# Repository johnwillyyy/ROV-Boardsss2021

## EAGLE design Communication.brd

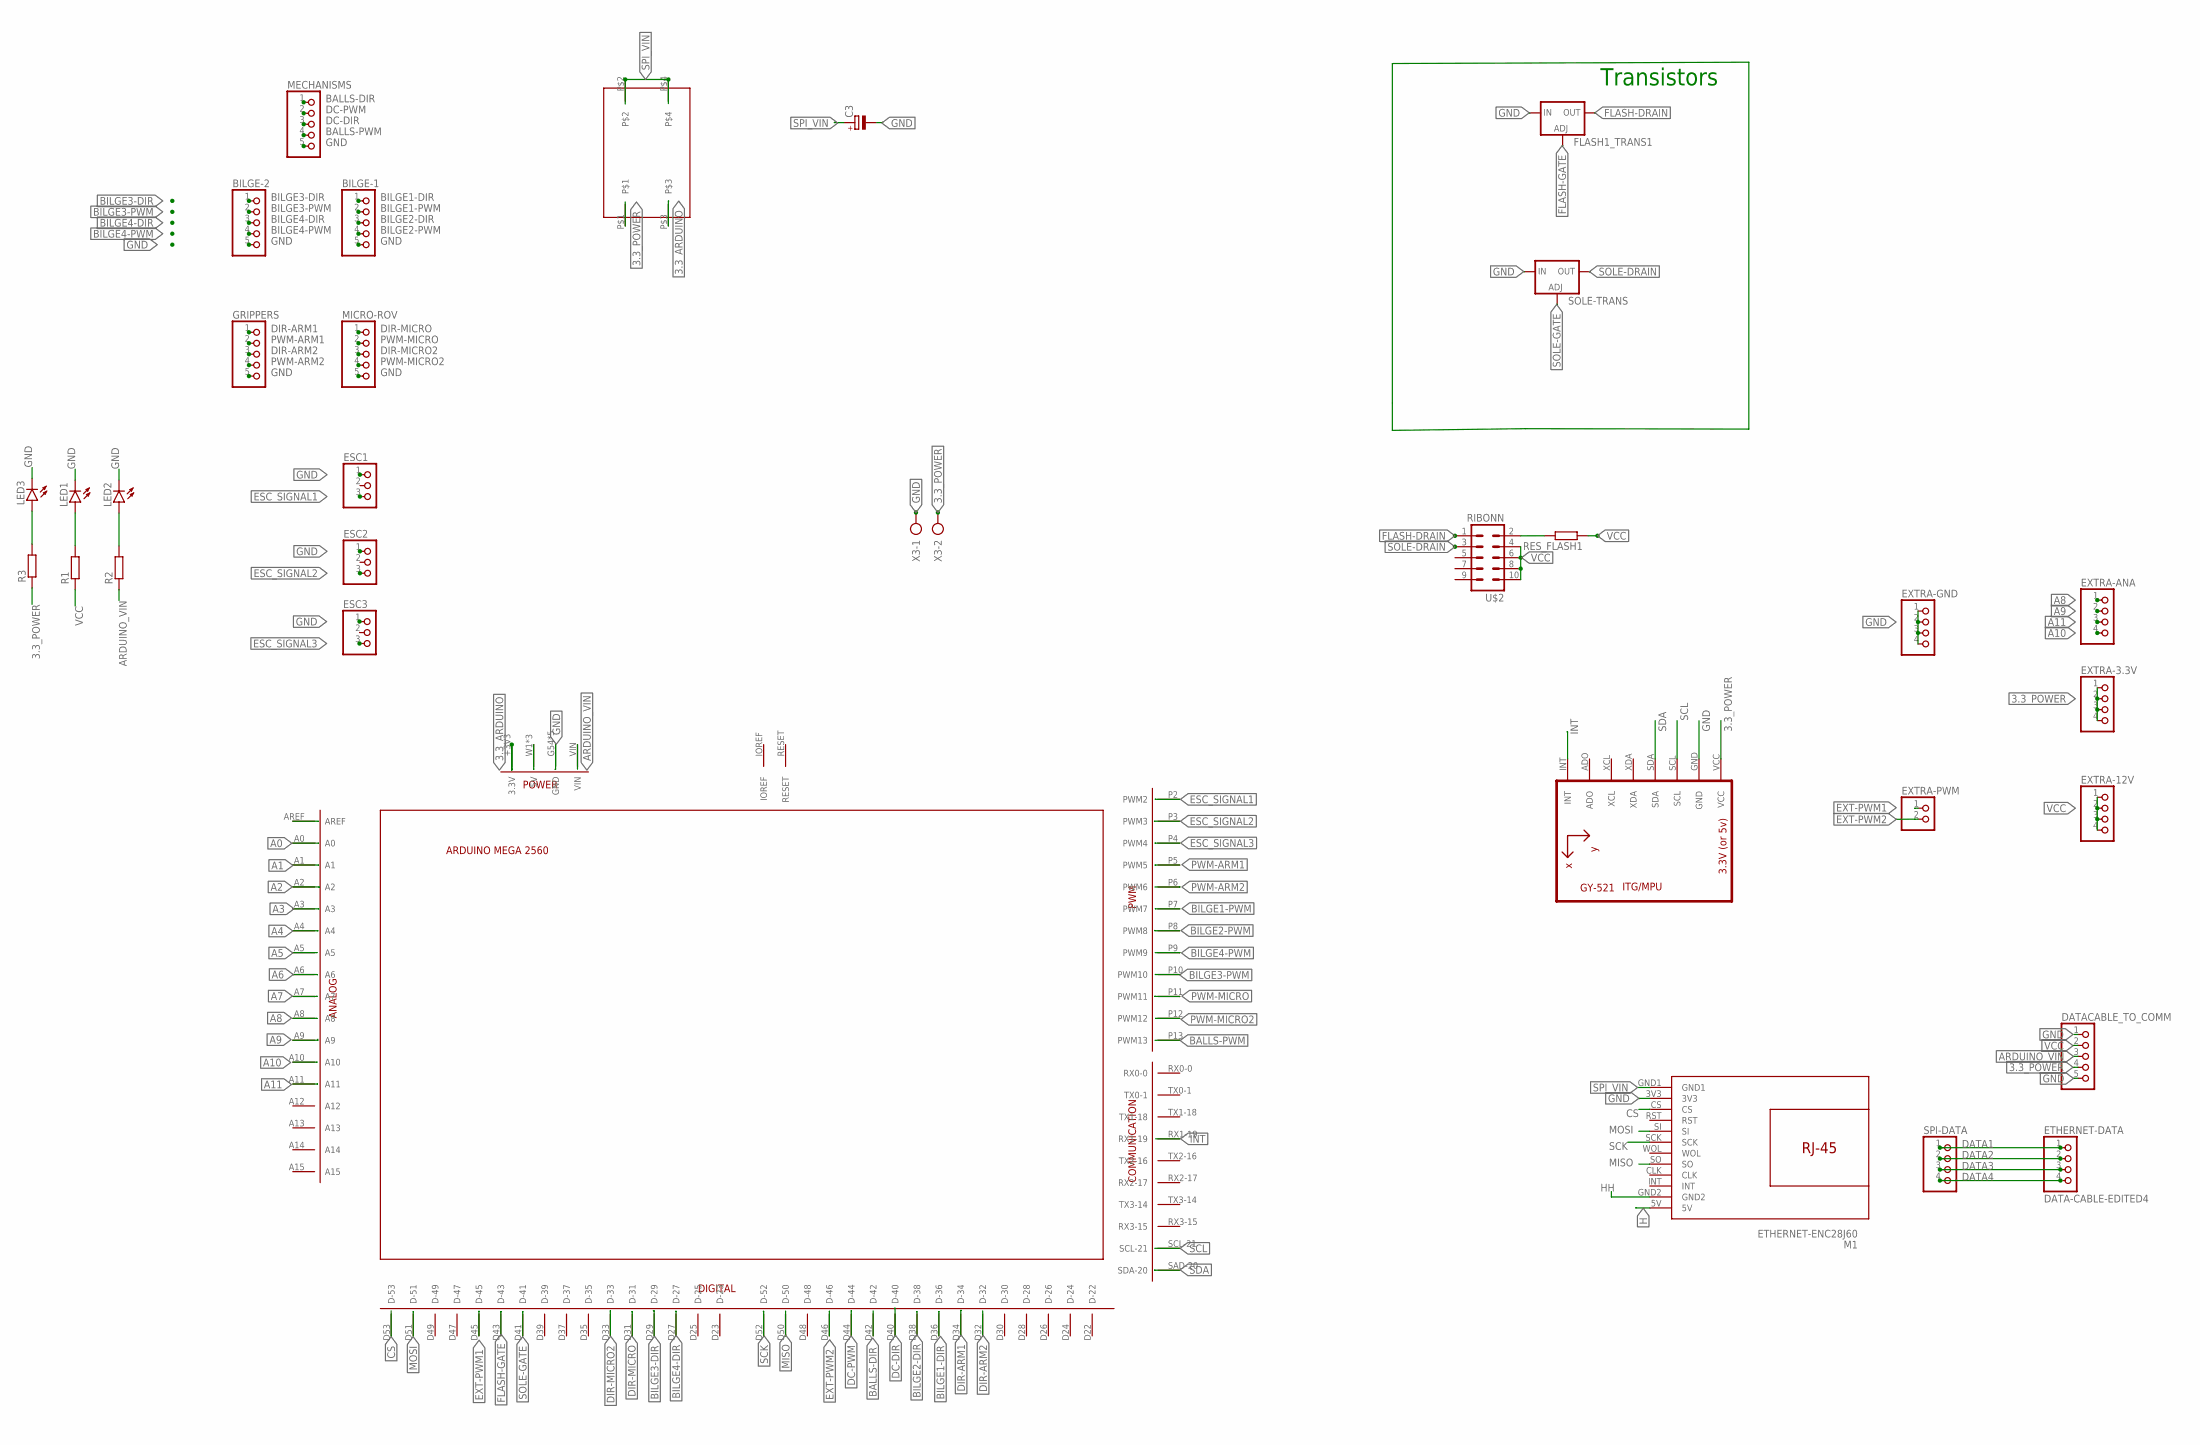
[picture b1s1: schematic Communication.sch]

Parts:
BILGE-1, BILGE-2: PINHD-1X5; 1X05
C3: CPOL-EUE3.5-8; E3,5-8
DATACABLE_TO_COMM: PINHD-1X5; 1X05
ESC1, ESC2, ESC3: PINHD-1X3; 1X03
ETHERNET-DATA: DATA-CABLE-EDITED4
EXTRA-3.3V, EXTRA-12V: PINHD-1X4; 1X04
EXTRA-ANA: PINHD-1X4; 1X04
EXTRA-GND: PINHD-1X4; 1X04
EXTRA-PWM: PINHD-1X2; 1X02
FLASH1_TRANS1: LM317TS; 317TS
GRIPPERS: PINHD-1X5; 1X05
LED1, LED2, LED3: LED3MM
M1: ETHERNET-ENC28J60
MECHANISMS: PINHD-1X5; 1X05
MICRO-ROV: PINHD-1X5; 1X05
R1, R2, R3: R-EU_0207/10; 0207/10
RES_FLASH1: R-EU_0207/10; 0207/10
SOLE-TRANS: LM317TS; 317TS
SPI-DATA: PINHD-1X4; 1X04
U2: GY-521MPU6050; GY-521
U$1: BOARD_ARDUINO-MEGA; BOARD_ARDUINO_MEGA
U$2: RIBONN
U$3: DIPSWITCH_2PINS
X3: AK300/2

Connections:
3.3_ARDUINO: U$1.+3V3 (3.3V), U$3.P$3
3.3_POWER: DATACABLE_TO_COMM.4, EXTRA-3.3V.1, EXTRA-3.3V.2, EXTRA-3.3V.3, EXTRA-3.3V.4, R3.1, U2.VCC, U$3.P$1, X3.2
A0: U$1.A0
A1: U$1.A1
A2: U$1.A2
A3: U$1.A3
A4: U$1.A4
A5: U$1.A5
A6: U$1.A6
A7: U$1.A7
A8: EXTRA-ANA.1, U$1.A8
A9: EXTRA-ANA.2, U$1.A9
A10: EXTRA-ANA.4, U$1.A10
A11: EXTRA-ANA.3, U$1.A11
ARDUINO_VIN: DATACABLE_TO_COMM.3, R2.1, U$1.VIN
BALLS-DIR: MECHANISMS.1, U$1.D42 (D-42)
BALLS-PWM: MECHANISMS.4, U$1.P13 (PWM13)
BILGE1-DIR: BILGE-1.1, U$1.D36 (D-36)
BILGE1-PWM: BILGE-1.2, U$1.P7 (PWM7)
BILGE2-DIR: BILGE-1.3, U$1.D38 (D-38)
BILGE2-PWM: BILGE-1.4, U$1.P8 (PWM8)
BILGE3-DIR: BILGE-2.1, U$1.D29 (D-29)
BILGE3-PWM: BILGE-2.2, U$1.P10 (PWM10)
BILGE4-DIR: BILGE-2.3, U$1.D27 (D-27)
BILGE4-PWM: BILGE-2.4, U$1.P9 (PWM9)
CS: M1.CS, U$1.D53 (D-53)
DATA1: ETHERNET-DATA.1, SPI-DATA.1
DATA2: ETHERNET-DATA.2, SPI-DATA.2
DATA3: ETHERNET-DATA.3, SPI-DATA.3
DATA4: ETHERNET-DATA.4, SPI-DATA.4
DC-DIR: MECHANISMS.3, U$1.D40 (D-40)
DC-PWM: MECHANISMS.2, U$1.D44 (D-44)
DIR-ARM1: GRIPPERS.1, U$1.D34 (D-34)
DIR-ARM2: GRIPPERS.3, U$1.D32 (D-32)
DIR-MICRO: MICRO-ROV.1, U$1.D31 (D-31)
DIR-MICRO2: MICRO-ROV.3, U$1.D33 (D-33)
ESC_SIGNAL1: ESC1.3, U$1.P2 (PWM2)
ESC_SIGNAL2: ESC2.3, U$1.P3 (PWM3)
ESC_SIGNAL3: ESC3.3, U$1.P4 (PWM4)
EXT-PWM1: EXTRA-PWM.1, U$1.D45 (D-45)
EXT-PWM2: EXTRA-PWM.2, U$1.D46 (D-46)
FLASH-DRAIN: FLASH1_TRANS1.2 (OUT), U$2.1
FLASH-GATE: FLASH1_TRANS1.1 (ADJ), U$1.D43 (D-43)
GND: BILGE-1.5, BILGE-2.5, C3.-, DATACABLE_TO_COMM.1, DATACABLE_TO_COMM.5, ESC1.1, ESC2.1, ESC3.1, EXTRA-GND.1, EXTRA-GND.2, EXTRA-GND.3, EXTRA-GND.4, FLASH1_TRANS1.3 (IN), GRIPPERS.5, LED1.K (C), LED2.K (C), LED3.K (C), M1.3V3, MECHANISMS.5, MICRO-ROV.5, SOLE-TRANS.3 (IN), U2.GND, U$1.G54 (GND), U$1.G55 (GND), U$1.G56 (GND), U$1.G57 (GND), U$1.G58 (GND), X3.1
H: M1.5V
HH: M1.GND2
INT: U2.INT, U$1.RX1-19
MISO: M1.SO, U$1.D50 (D-50)
MOSI: M1.SI, U$1.D51 (D-51)
unnamed: LED1.A, R1.2
unnamed: LED2.A, R2.2
unnamed: RES_FLASH1.2, U$2.2
unnamed: LED3.A, R3.2
unnamed: U$1.W1 (5V), U$1.W2 (5V), U$1.W3 (5V)
PWM-ARM1: GRIPPERS.2, U$1.P5 (PWM5)
PWM-ARM2: GRIPPERS.4, U$1.P6 (PWM6)
PWM-MICRO: MICRO-ROV.2, U$1.P11 (PWM11)
PWM-MICRO2: MICRO-ROV.4, U$1.P12 (PWM12)
SCK: M1.SCK, U$1.D52 (D-52)
SCL: U2.SCL, U$1.SCL-21
SDA: U2.SDA, U$1.SAD-20 (SDA-20)
SOLE-DRAIN: SOLE-TRANS.2 (OUT), U$2.3
SOLE-GATE: SOLE-TRANS.1 (ADJ), U$1.D41 (D-41)
SPI_VIN: C3.+, M1.GND1, U$3.P$2, U$3.P$4
VCC: DATACABLE_TO_COMM.2, EXTRA-12V.1, EXTRA-12V.2, EXTRA-12V.3, EXTRA-12V.4, R1.1, RES_FLASH1.1, U$2.4, U$2.6, U$2.8, U$2.10

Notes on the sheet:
Transistors

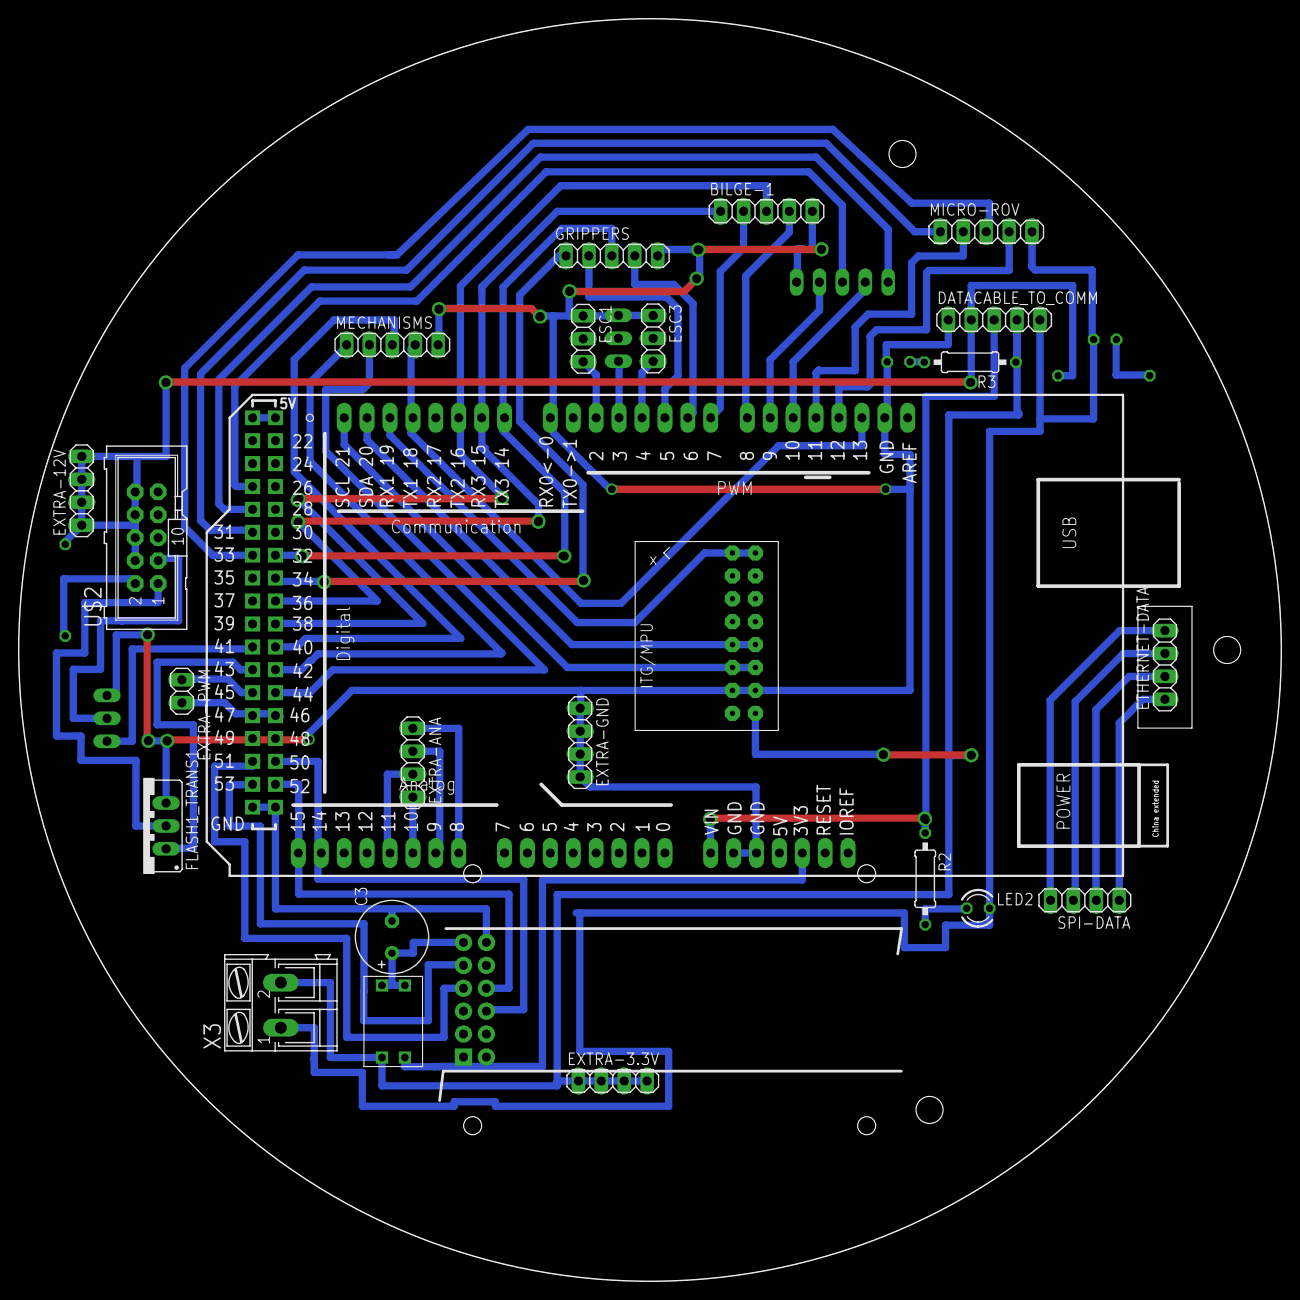
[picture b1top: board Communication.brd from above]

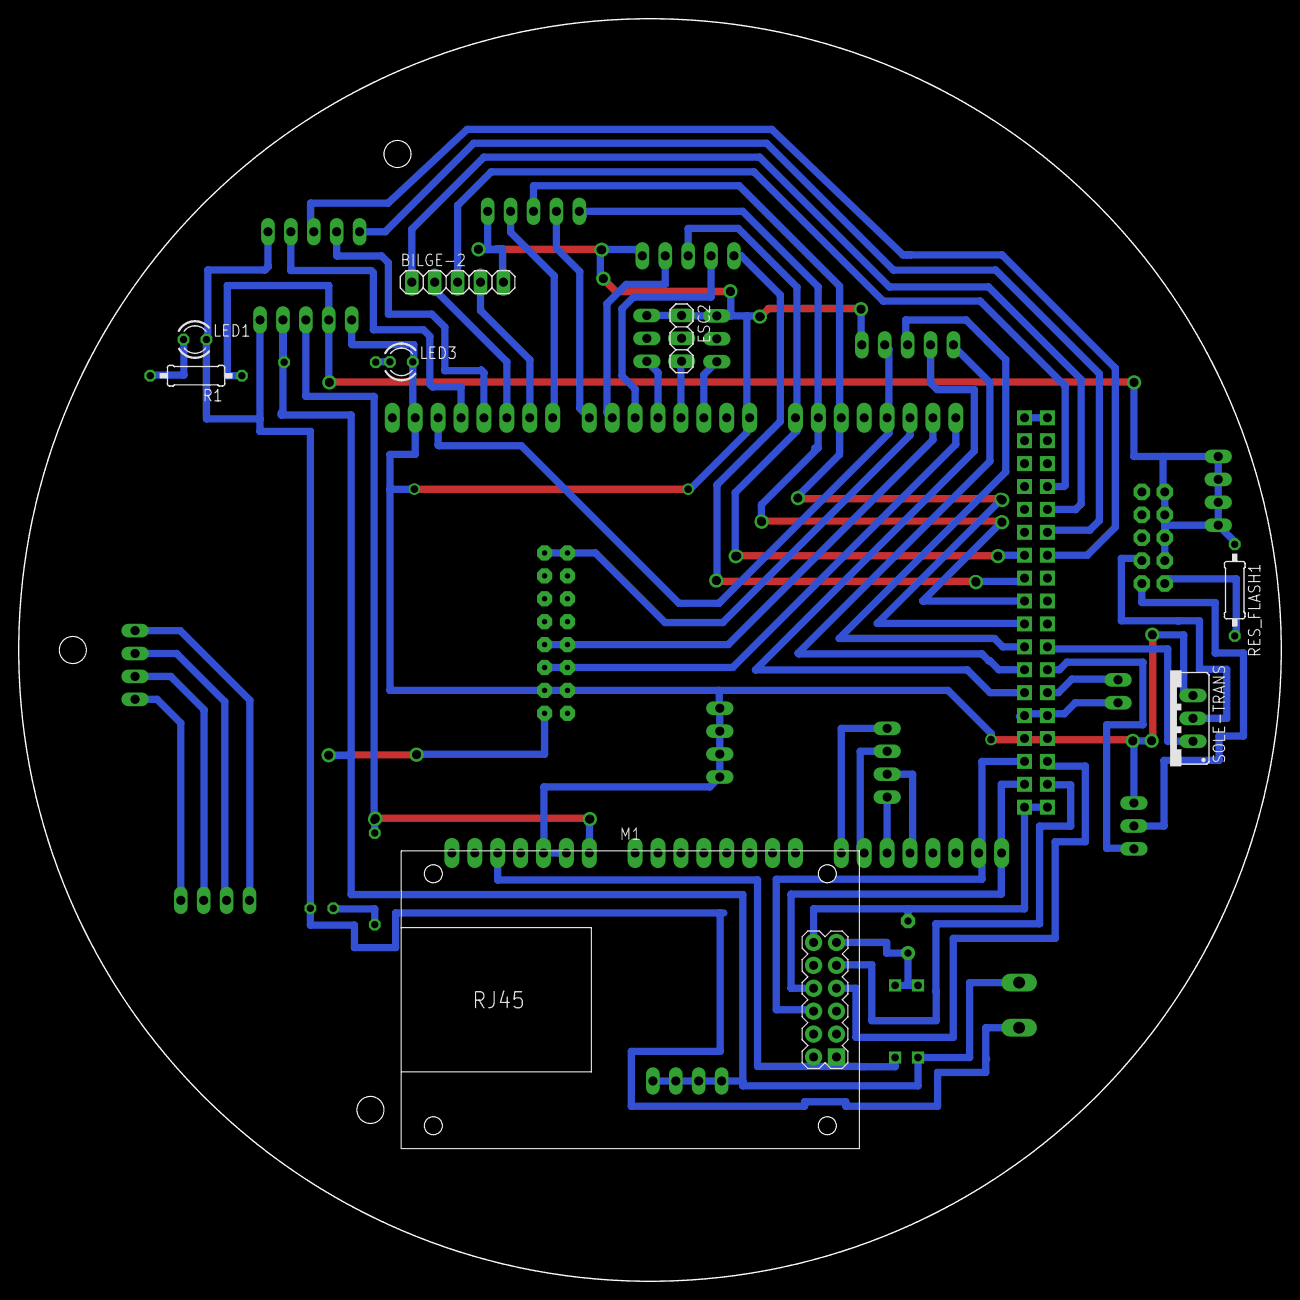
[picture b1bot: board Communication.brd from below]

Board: 2 copper layers, 140.0 x 140.0 mm, 32 parts (8 on the bottom side), 55 nets.

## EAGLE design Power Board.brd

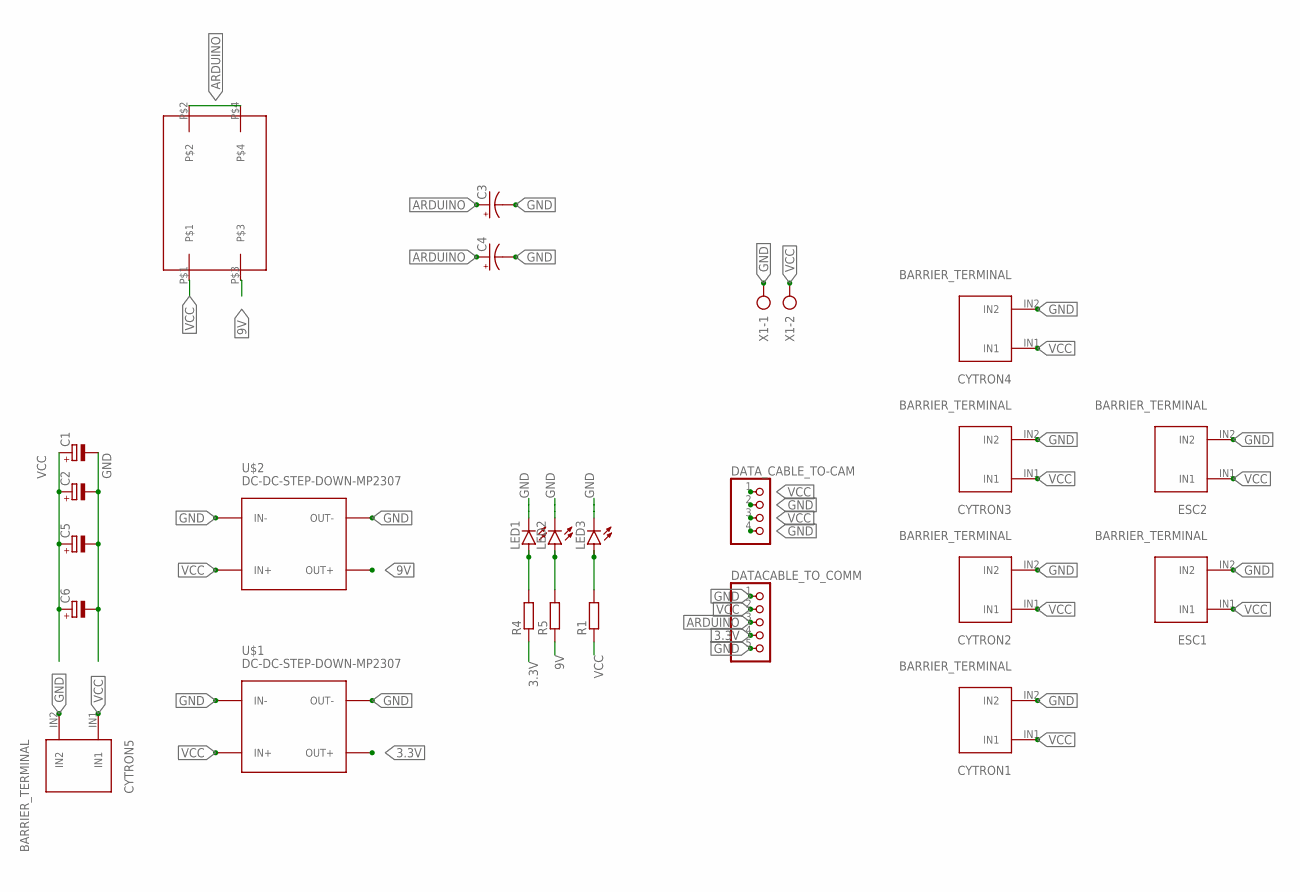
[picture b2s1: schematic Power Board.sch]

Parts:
C1, C2, C5, C6: CPOL-EUE7.5-16; E7,5-16
C3, C4: CPOL-USE5-13; E5-13
CYTRON1, CYTRON2, CYTRON3, CYTRON4, CYTRON5: BARRIER_TERMINAL
DATACABLE_TO_COMM: PINHD-1X5; 1X05
DATA_CABLE_TO-CAM: PINHD-1X4; 1X04
ESC1, ESC2: BARRIER_TERMINAL
LED1, LED2, LED3: LED3MM
R1, R4, R5: R-EU_0204/7; 0204/7
U$1, U$2: DC-DC-STEP-DOWN-MP2307
U$3: DIPSWITCH_2PINS
X1: AK300/2

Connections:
3.3V: DATACABLE_TO_COMM.4, R4.1, U$1.OUT+
9V: R5.1, U$2.OUT+, U$3.P$3
ARDUINO: C3.+, C4.+, DATACABLE_TO_COMM.3, U$3.P$2, U$3.P$4
GND: C1.-, C2.-, C3.-, C4.-, C5.-, C6.-, CYTRON1.IN2, CYTRON2.IN2, CYTRON3.IN2, CYTRON4.IN2, CYTRON5.IN2, DATACABLE_TO_COMM.1, DATACABLE_TO_COMM.5, DATA_CABLE_TO-CAM.2, DATA_CABLE_TO-CAM.4, ESC1.IN2, ESC2.IN2, LED1.K (C), LED2.K (C), LED3.K (C), U$1.IN-, U$1.OUT-, U$2.IN-, U$2.OUT-, X1.1
unnamed: LED3.A, R1.2
unnamed: LED1.A, R4.2
unnamed: LED2.A, R5.2
VCC: C1.+, C2.+, C5.+, C6.+, CYTRON1.IN1, CYTRON2.IN1, CYTRON3.IN1, CYTRON4.IN1, CYTRON5.IN1, DATACABLE_TO_COMM.2, DATA_CABLE_TO-CAM.1, DATA_CABLE_TO-CAM.3, ESC1.IN1, ESC2.IN1, R1.1, U$1.IN+, U$2.IN+, U$3.P$1, X1.2

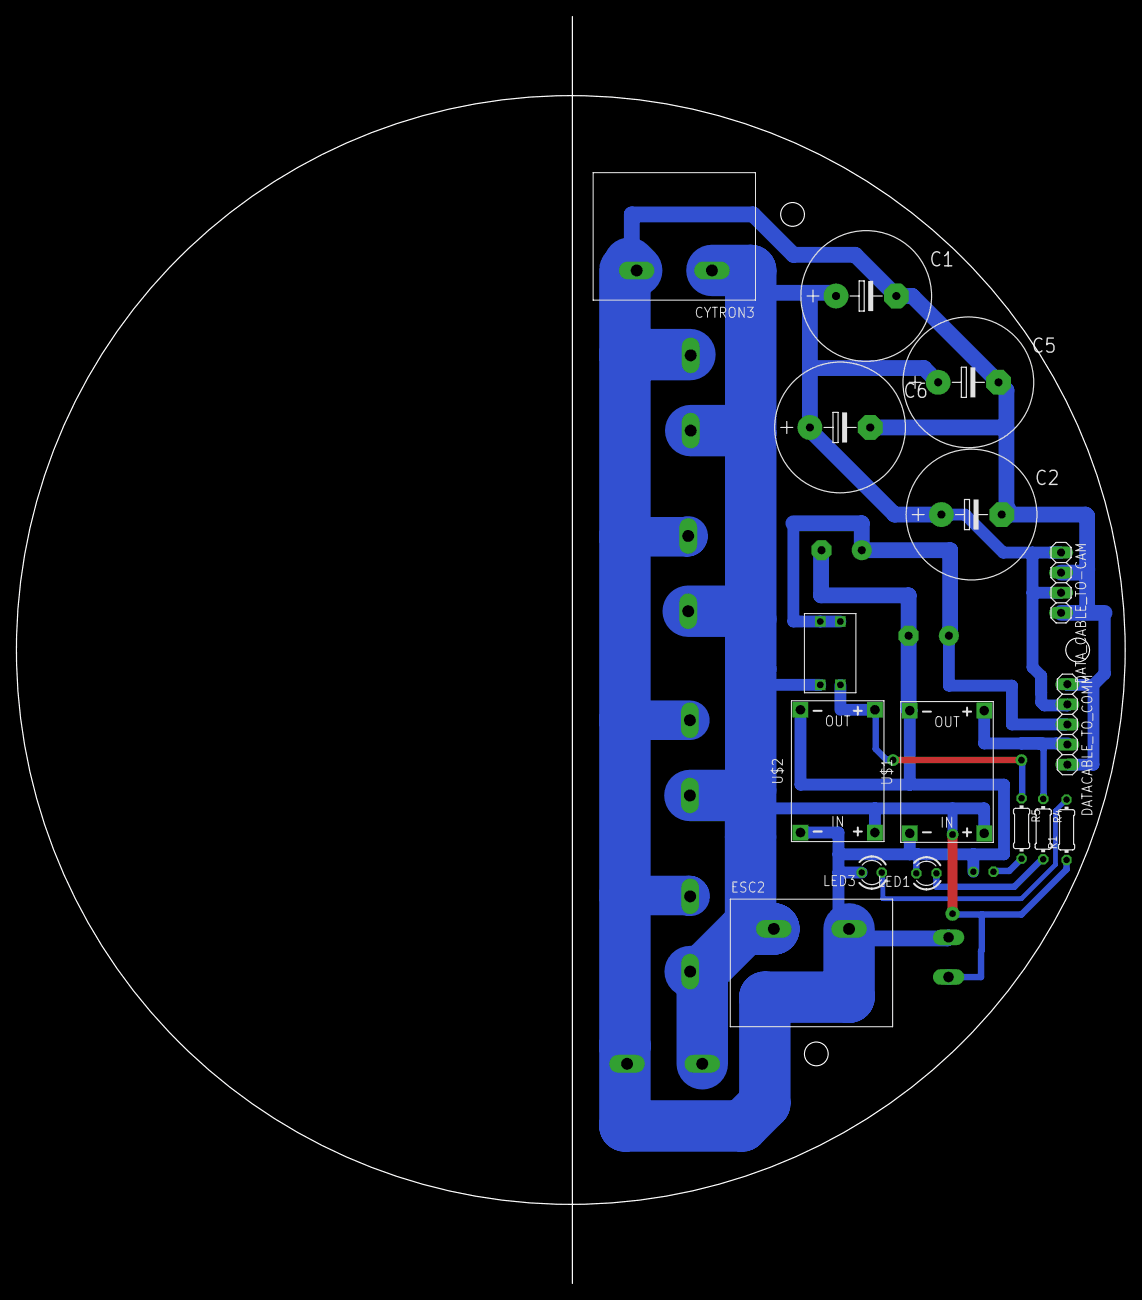
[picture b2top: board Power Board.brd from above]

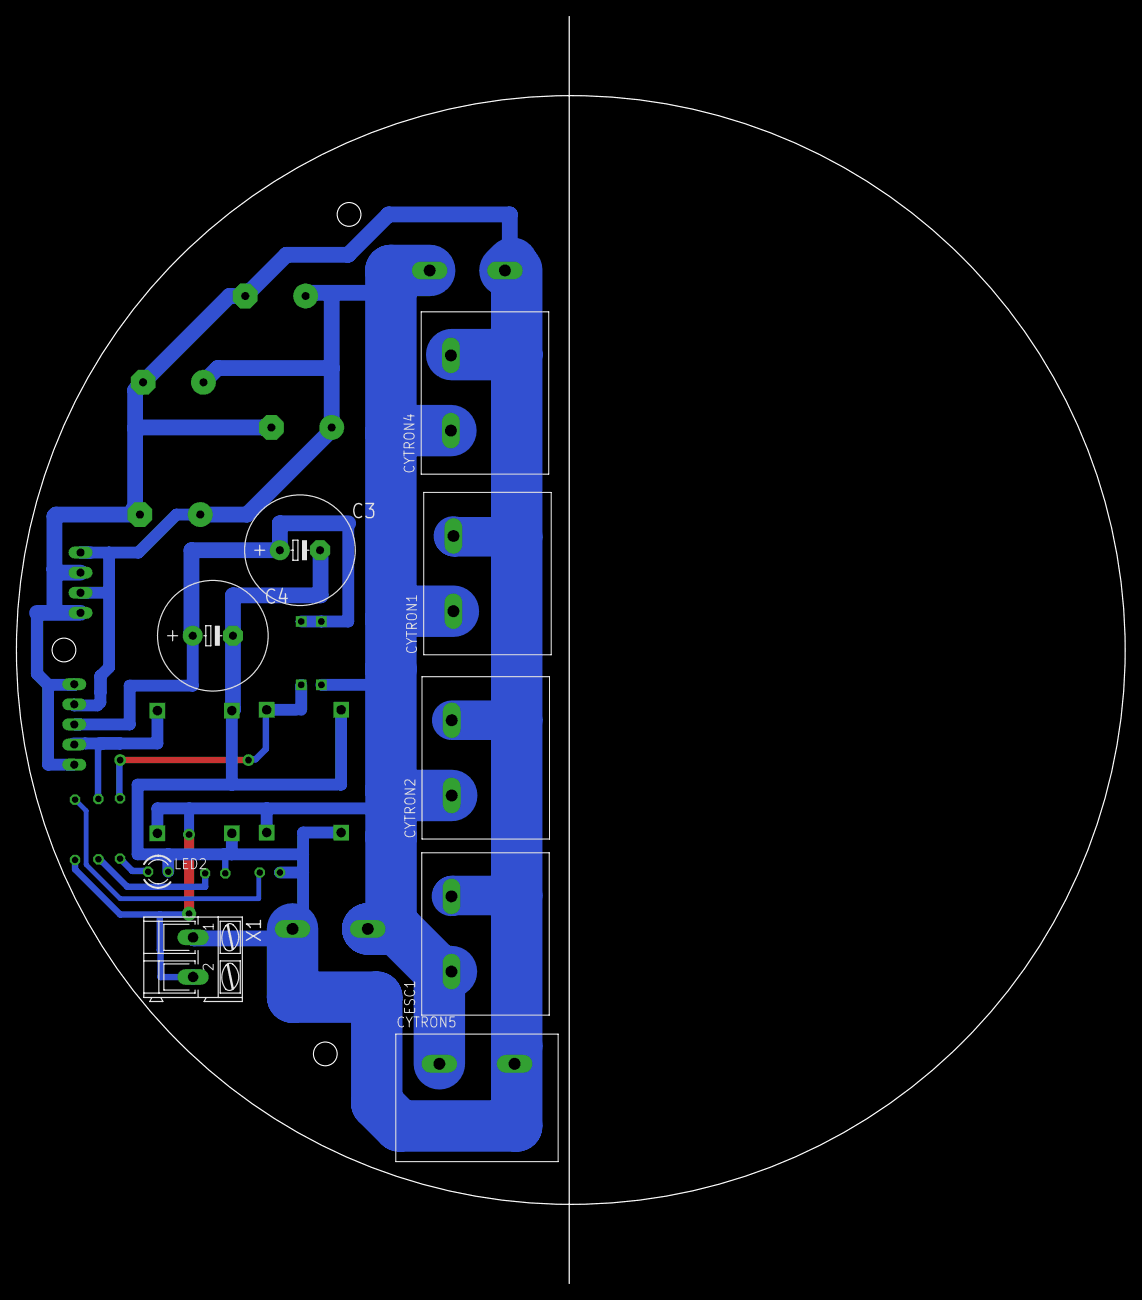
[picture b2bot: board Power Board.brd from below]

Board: 2 copper layers, 140.0 x 140.0 mm, 25 parts (9 on the bottom side), 8 nets.

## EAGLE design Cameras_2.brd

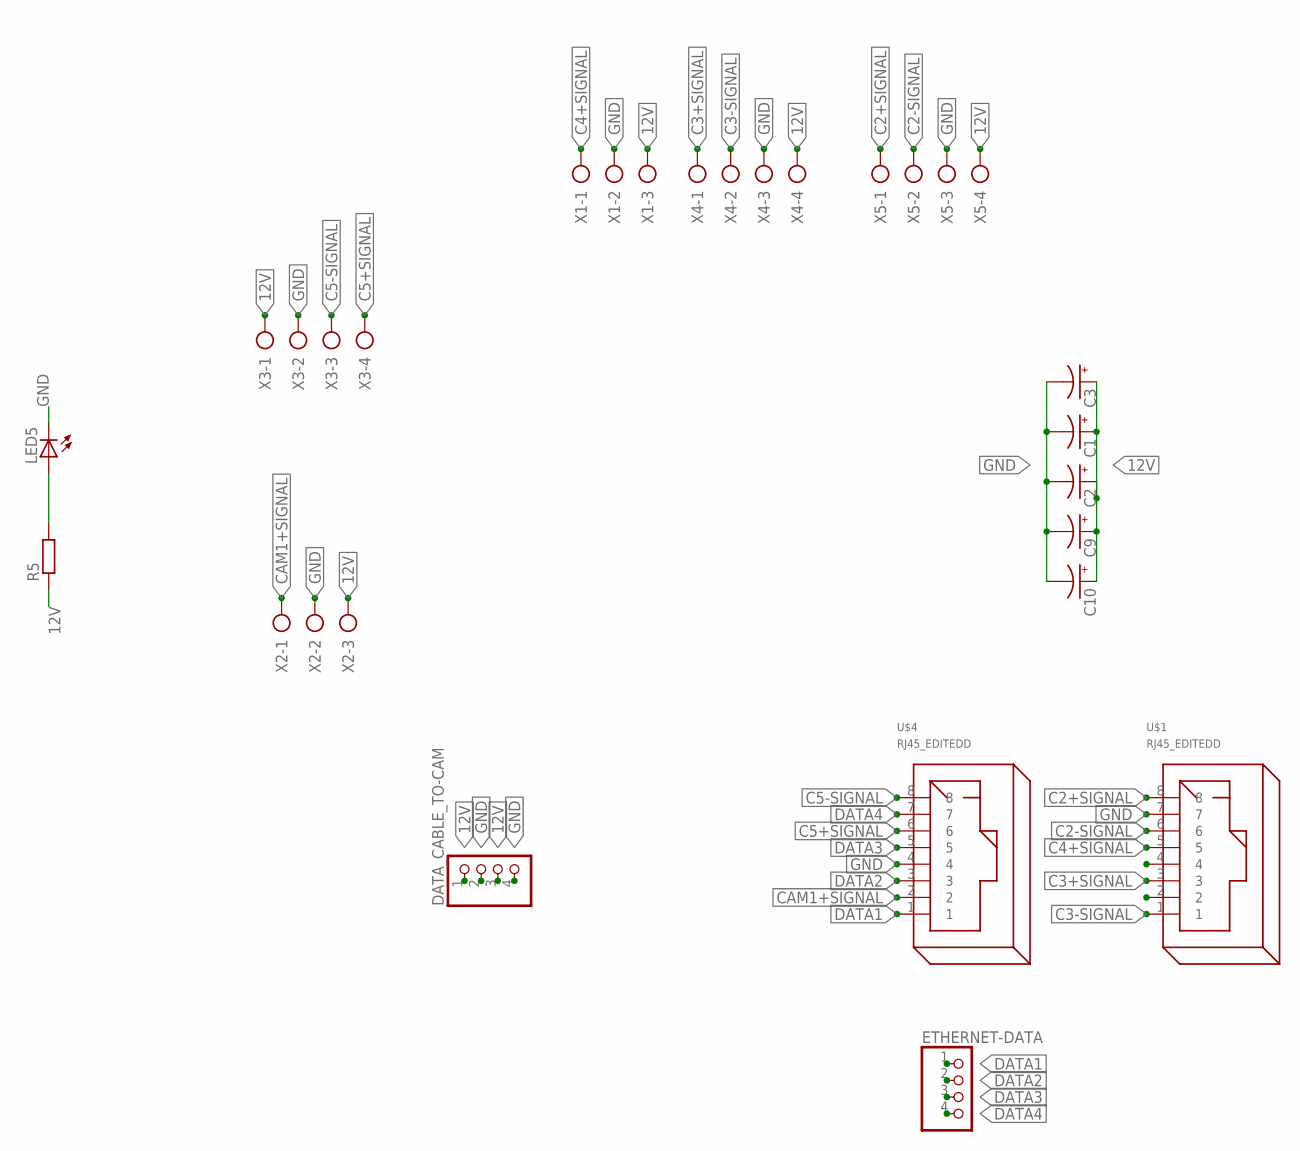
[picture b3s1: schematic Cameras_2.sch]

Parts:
C1, C2, C3, C9, C10: CPOL-USE2,5-6E; E2,5-6E
DATA_CABLE_TO-CAM: PINHD-1X4; 1X04
ETHERNET-DATA: PINHD-1X4; 1X04
LED5: LEDCHIPLED_1206; CHIPLED_1206
R5: R-EU_0204/7; 0204/7
U$1, U$4: RJ45_EDITEDD; RJ45
X1, X2: AK300/3
X3, X4, X5: AK300/4

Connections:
12V: C1.+, C2.+, C3.+, C9.+, C10.+, DATA_CABLE_TO-CAM.1, DATA_CABLE_TO-CAM.3, R5.1, X1.3, X2.3, X3.1, X4.4, X5.4
C2+SIGNAL: U$1.8, X5.1
C2-SIGNAL: U$1.6, X5.2
C3+SIGNAL: U$1.3, X4.1
C3-SIGNAL: U$1.1, X4.2
C4+SIGNAL: U$1.5, X1.1
C5+SIGNAL: U$4.6, X3.4
C5-SIGNAL: U$4.8, X3.3
CAM1+SIGNAL: U$4.2, X2.1
DATA1: ETHERNET-DATA.1, U$4.1
DATA2: ETHERNET-DATA.2, U$4.3
DATA3: ETHERNET-DATA.3, U$4.5
DATA4: ETHERNET-DATA.4, U$4.7
GND: C1.-, C2.-, C3.-, C9.-, C10.-, DATA_CABLE_TO-CAM.2, DATA_CABLE_TO-CAM.4, LED5.C, U$1.7, U$4.4, X1.2, X2.2, X3.2, X4.3, X5.3
unnamed: LED5.A, R5.2

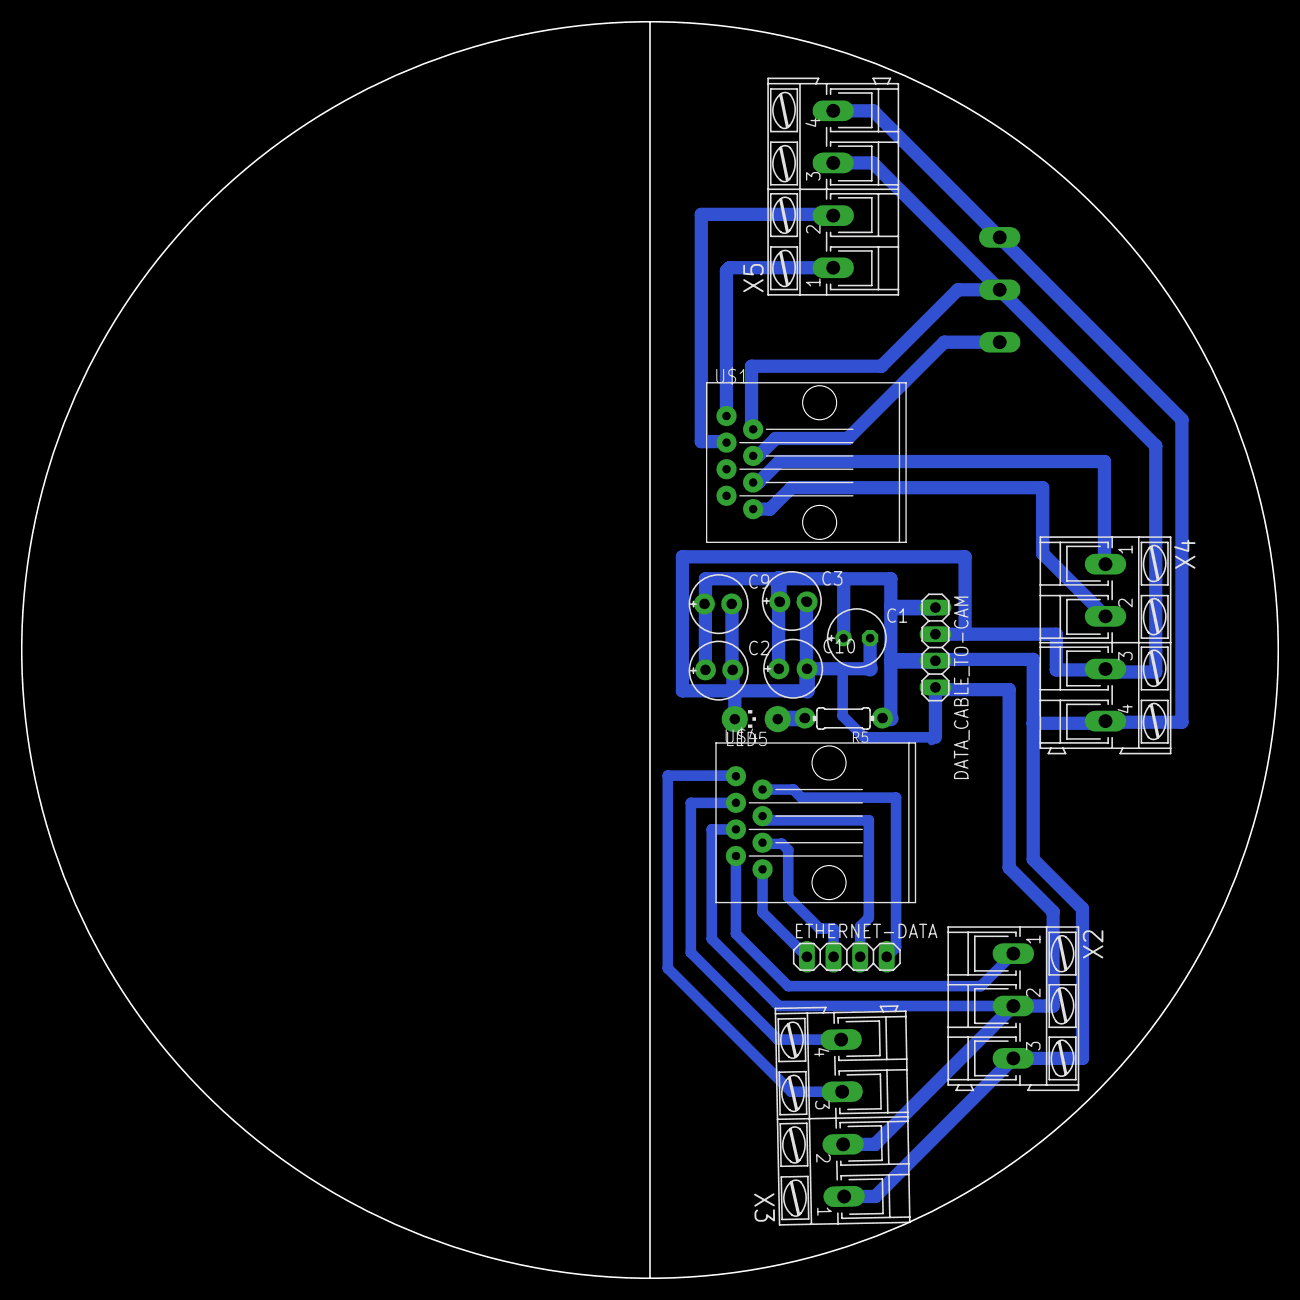
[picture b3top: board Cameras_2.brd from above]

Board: 2 copper layers, 120.0 x 120.0 mm, 16 parts (1 on the bottom side), 15 nets.

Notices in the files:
parts and their libraries:
Ethernet_TO_SPI Module: Released under the Creative Commons Attribution 4.0 International License: http://creativecommons.org/licenses/by/4.0
dipswitch_2pins: Copyright: Würth Elektronik
